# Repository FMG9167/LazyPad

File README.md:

# LazyPad
LazyPad is a Macropad made up of 6 keys.

This is my first time creating and submitting anything in HackClub!

## CAD
Used Autodesk Fusion to make this.

## PCB
The PCB was made using KiCAD.

[Find the cursor if you can :P]

## Firmware
KMK was used to make the firmware of the pad.

## BOM

- 6x MX Switched (I dont know much about them any will work i think)
- 1x XIAO RP2040
- 4x M3x5x4 Heatset inserts
- 4x M3x16mm screws

## Notes
This was my first time using Fusion and KiCAD but man it worth the time.

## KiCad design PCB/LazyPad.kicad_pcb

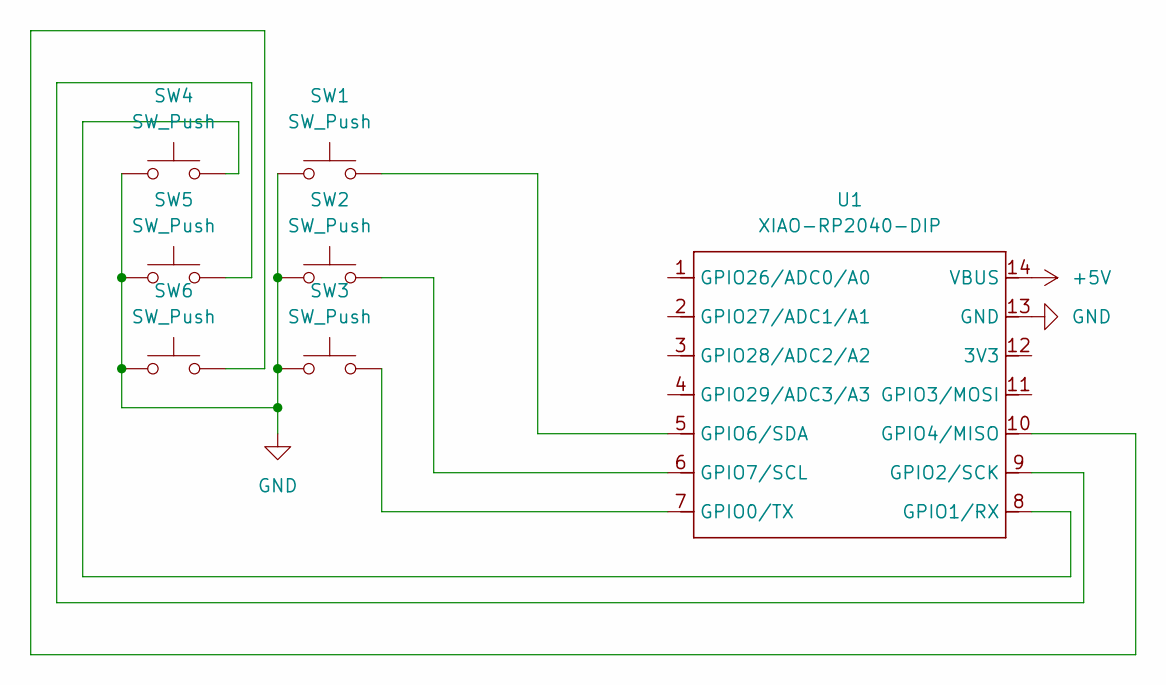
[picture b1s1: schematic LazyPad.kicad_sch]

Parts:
SW1, SW2, SW3, SW4, SW5, SW6: SW_Push; SW_Cherry_MX_1.00u_PCB
U1: XIAO-RP2040-DIP

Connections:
+5V: U1.14 (VBUS)
GND: SW1.1, SW2.1, SW3.1, SW4.1, SW5.1, SW6.1, U1.13 (GND)
unnamed: SW3.2, U1.7 (GPIO0/TX)
unnamed: SW4.2, U1.8 (GPIO1/RX)
unnamed: SW5.2, U1.9 (GPIO2/SCK)
unnamed: SW6.2, U1.10 (GPIO4/MISO)
unnamed: SW1.2, U1.5 (GPIO6/SDA)
unnamed: SW2.2, U1.6 (GPIO7/SCL)

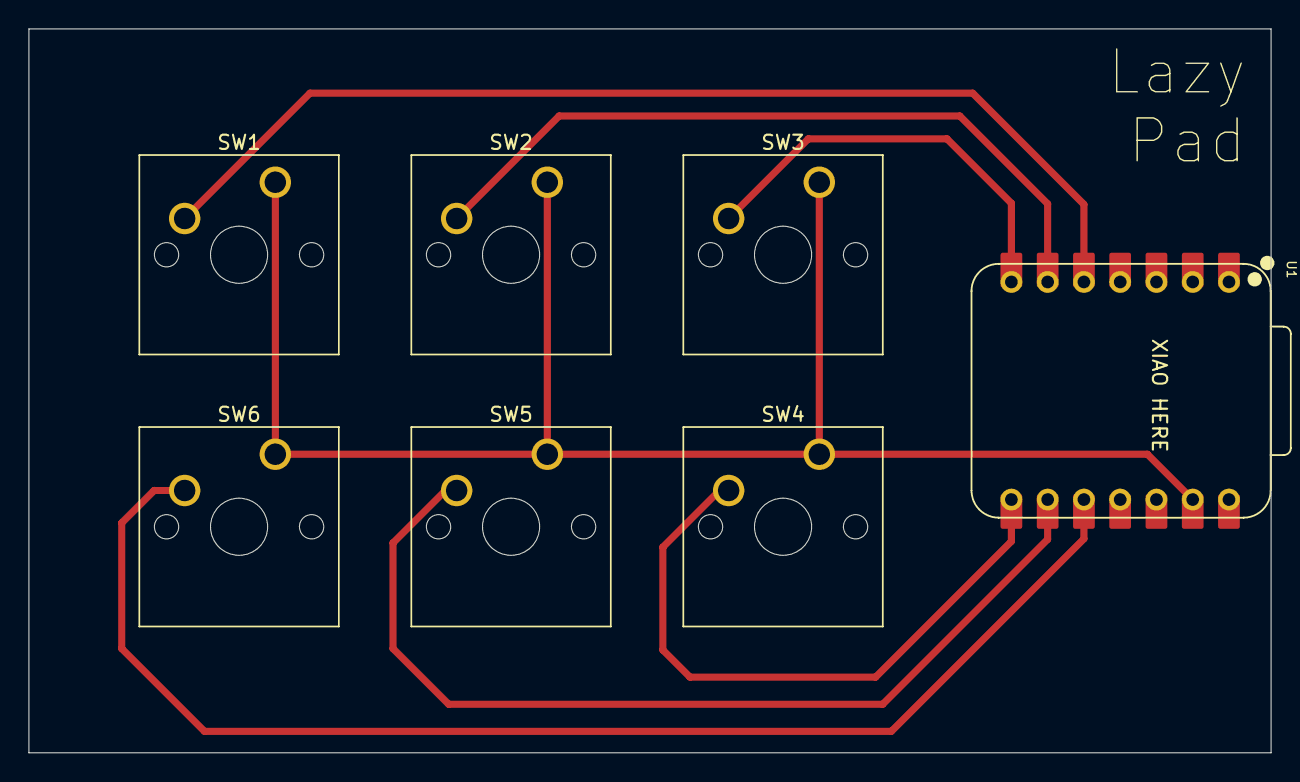
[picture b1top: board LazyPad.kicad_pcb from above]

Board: 2 copper layers, 87.0 x 50.7 mm, 7 parts (0 on the bottom side), 7 nets.

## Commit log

2025-06-23 added rest of the stuff
